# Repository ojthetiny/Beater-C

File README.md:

# beater-c
 an elite-c replacement

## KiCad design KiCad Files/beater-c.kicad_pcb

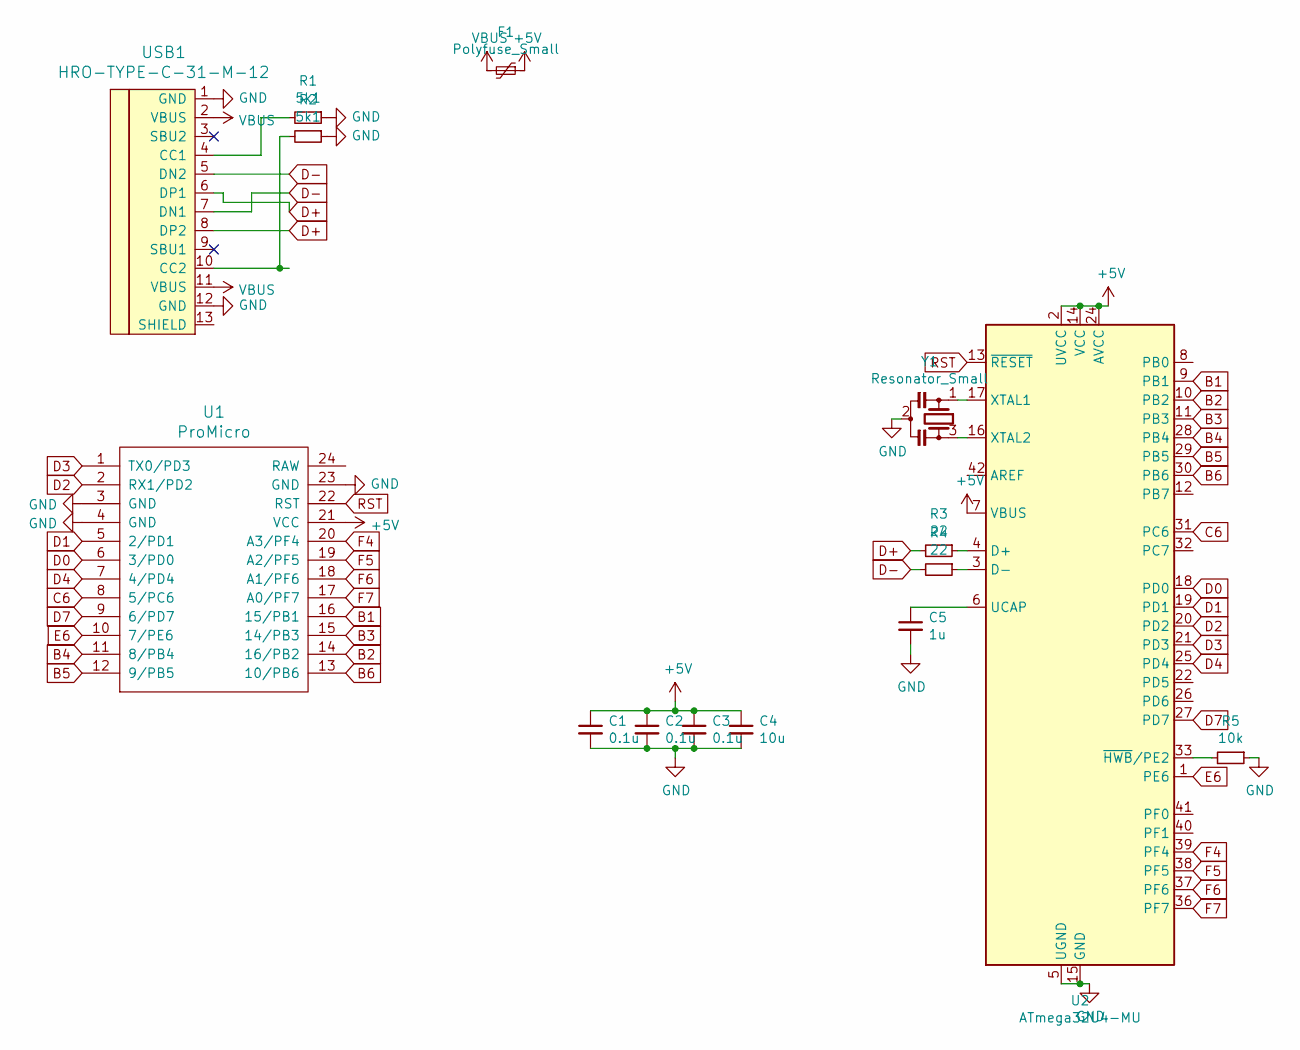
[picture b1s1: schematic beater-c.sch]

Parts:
C1, C2, C3: 0.1u; R_0402_1005Metric
C4: 10u; R_0402_1005Metric
C5: 1u; R_0402_1005Metric
F1: Polyfuse_Small; Fuse_0805_2012Metric
R1, R2: 5k1; R_0402_1005Metric
R3, R4: 22; R_0402_1005Metric
R5: 10k; R_0402_1005Metric
U1: ProMicro; ArduinoProMicro
U2: ATmega32U4-MU; QFN-44-1EP_7x7mm_P0.5mm_EP5.2x5.2mm
USB1: HRO-TYPE-C-31-M-12; USB-C-12-Pin-MidMount
Y1: Resonator_Small; Resonator_SMD_muRata_CSTxExxV-3Pin_3.0x1.1mm

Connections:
+5V: C1.1, C2.1, C3.1, C4.1, F1.1, U1.21 (VCC), U2.2 (UVCC), U2.7 (VBUS), U2.14 (VCC), U2.24 (AVCC), U2.34 (VCC), U2.44 (AVCC)
B1: U1.16 (15/PB1), U2.9 (PB1)
B2: U1.14 (16/PB2), U2.10 (PB2)
B3: U1.15 (14/PB3), U2.11 (PB3)
B4: U1.11 (8/PB4), U2.28 (PB4)
B5: U1.12 (9/PB5), U2.29 (PB5)
B6: U1.13 (10/PB6), U2.30 (PB6)
C6: U1.8 (5/PC6), U2.31 (PC6)
D0: U1.6 (3/PD0), U2.18 (PD0)
D1: U1.5 (2/PD1), U2.19 (PD1)
D2: U1.2 (RX1/PD2), U2.20 (PD2)
D3: U1.1 (TX0/PD3), U2.21 (PD3)
D4: U1.7 (4/PD4), U2.25 (PD4)
D7: U1.9 (6/PD7), U2.27 (PD7)
D+: R3.2, USB1.6 (DP1), USB1.8 (DP2)
D-: R4.2, USB1.5 (DN2), USB1.7 (DN1)
E6: U1.10 (7/PE6), U2.1 (PE6)
F4: U1.20 (A3/PF4), U2.39 (PF4)
F5: U1.19 (A2/PF5), U2.38 (PF5)
F6: U1.18 (A1/PF6), U2.37 (PF6)
F7: U1.17 (A0/PF7), U2.36 (PF7)
GND: C1.2, C2.2, C3.2, C4.2, C5.2, R1.1, R2.1, R5.1, U1.3 (GND), U1.4 (GND), U1.23 (GND), U2.5 (UGND), U2.15 (GND), U2.23 (GND), U2.35 (GND), U2.43 (GND), U2.45 (GND), USB1.1 (GND), USB1.12 (GND), Y1.2
unnamed: C5.1, U2.6 (UCAP)
unnamed: R1.2, USB1.4 (CC1)
unnamed: R2.2, USB1.10 (CC2)
unnamed: R3.1, U2.4 (D+)
unnamed: R4.1, U2.3 (D-)
unnamed: R5.2, U2.33 (~HWB~/PE2)
unnamed: U2.16 (XTAL2), Y1.3
unnamed: U2.17 (XTAL1), Y1.1
RST: U1.22 (RST), U2.13 (~RESET)
VBUS: F1.2, USB1.2 (VBUS), USB1.11 (VBUS)

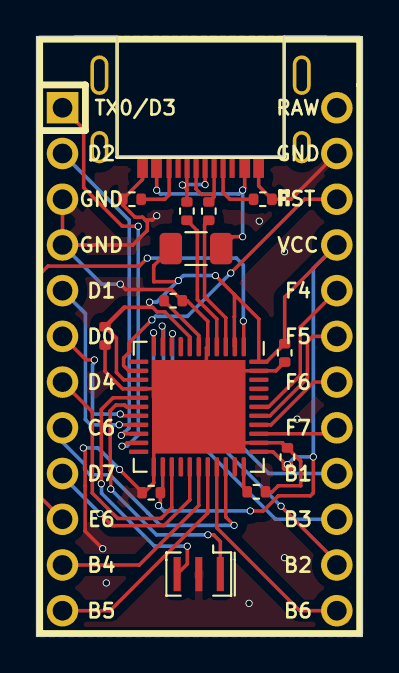
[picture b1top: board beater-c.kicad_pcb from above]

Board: 2 copper layers, 18.1 x 33.3 mm, 15 parts (0 on the bottom side), 32 nets.

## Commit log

2021-03-01 Added License
